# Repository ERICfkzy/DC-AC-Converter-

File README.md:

THT VERSION OF PCB
All components changed to through hole

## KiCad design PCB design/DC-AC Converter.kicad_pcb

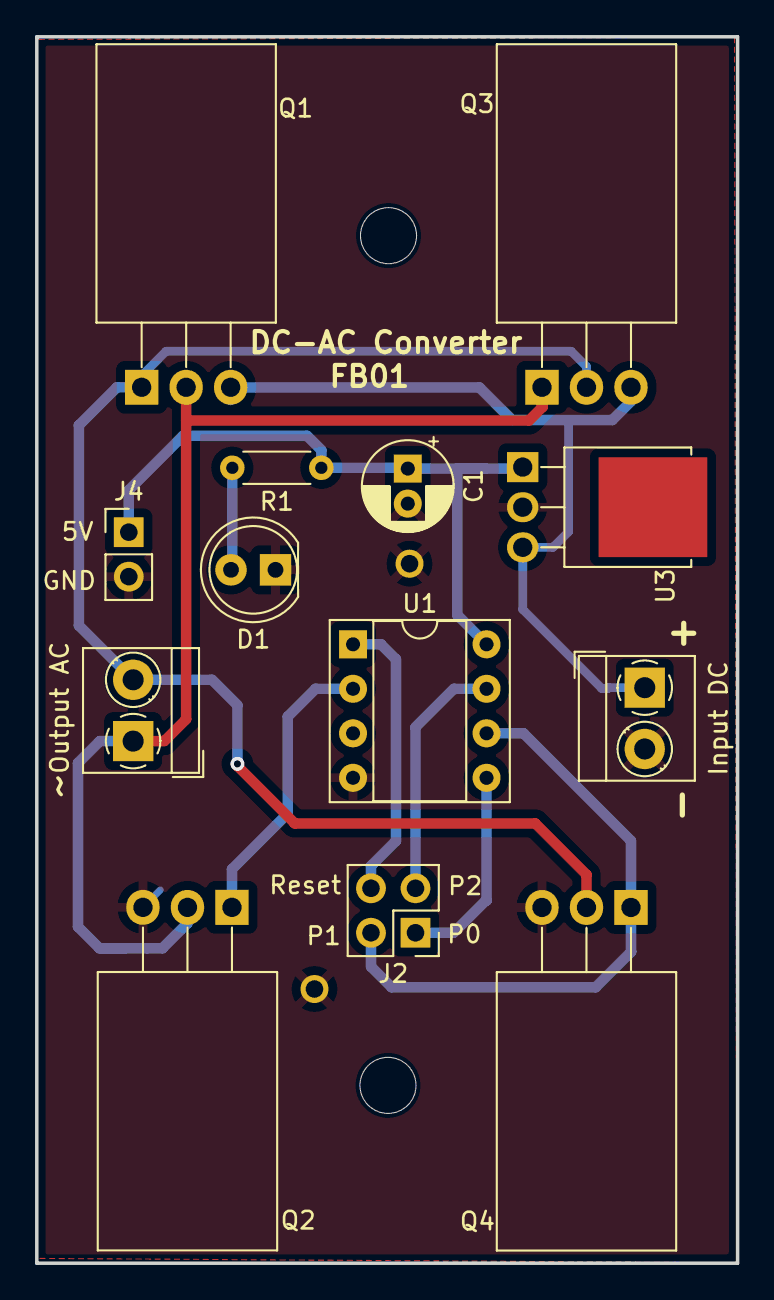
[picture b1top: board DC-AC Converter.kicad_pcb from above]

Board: 2 copper layers, 40.0 x 70.0 mm, 17 parts (0 on the bottom side), 11 nets.

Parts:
C1: C_Polarized_Small_US; CP_Radial_D5.0mm_P2.00mm
D1: LED; LED_D5.0mm
H1, H2: MountingHole_Pad; MountingHole_2.2mm_M2_DIN965_Pad_TopBottom
H3, H4: MountingHole; MountingHole_3.2mm_M3
Input DC : Screw_Terminal_3.5mm_2; TerminalBlock_MetzConnect_Type059_RT06302HBWC_1x02_P3.50mm_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
J2: Conn_02x02_Counter_Clockwise; PinHeader_2x02_P2.54mm_Vertical
J4: Conn_01x02; PinHeader_1x02_P2.54mm_Vertical
Output AC: Screw_Terminal_3.5mm_2; TerminalBlock_MetzConnect_Type059_RT06302HBWC_1x02_P3.50mm_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
Q1, Q3: IRF9540N; TO-220-3_Horizontal_TabDown
Q2, Q4: IRFZ44NSTRLPBF; TO-220-3_Horizontal_TabDown
R1: 330; R_Axial_DIN0204_L3.6mm_D1.6mm_P5.08mm_Horizontal
U1: ATtiny85V-10P; DIP-8_W7.62mm_Socket
U3: L78L05_SOT89; TO-251-3-1EP_Horizontal_TabDown

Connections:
/Reset: J2.4, U1.1 (~RESET/PB5)
/pin0: J2.1, U1.5 (AREF/PB0)
/pin1: J2.2, Q4.1, U1.6 (PB1)
/pin2: J2.3, U1.7 (PB2)
GND: C1.2, D1.1 (K), H1.1, H2.1, Input DC.2, J4.2, Q2.3, Q4.3, U1.4 (GND), U3.2 (GND)
unnamed: D1.2 (A), R1.2
unnamed: Output AC.1, Q1.2 (D), Q2.2, Q3.1 (G)
unnamed: Output AC.2, Q1.1 (G), Q3.2 (D), Q4.2
unnamed: Input DC.1, Q1.3 (S), Q3.3 (S), U3.3 (IN)
unnamed: C1.1, J4.1, R1.1, U1.8 (VCC), U3.1 (OUT)
unnamed: Q2.1, U1.2 (XTAL1/PB3)

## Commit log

2025-04-29 Schematic diagram added
2025-04-29 SMD PCB created
2025-04-29 some SMD components changed to PTH footprint
2025-04-30 PCB/Board added
2025-04-30 THT version of PCB
2025-05-02 Improved the routing of PCB
2025-05-03 Improved silk screen and branded the PCB with FundiBots logo
2025-05-05 Improved on PCB
2025-05-09 improved on the labelling of input and output
